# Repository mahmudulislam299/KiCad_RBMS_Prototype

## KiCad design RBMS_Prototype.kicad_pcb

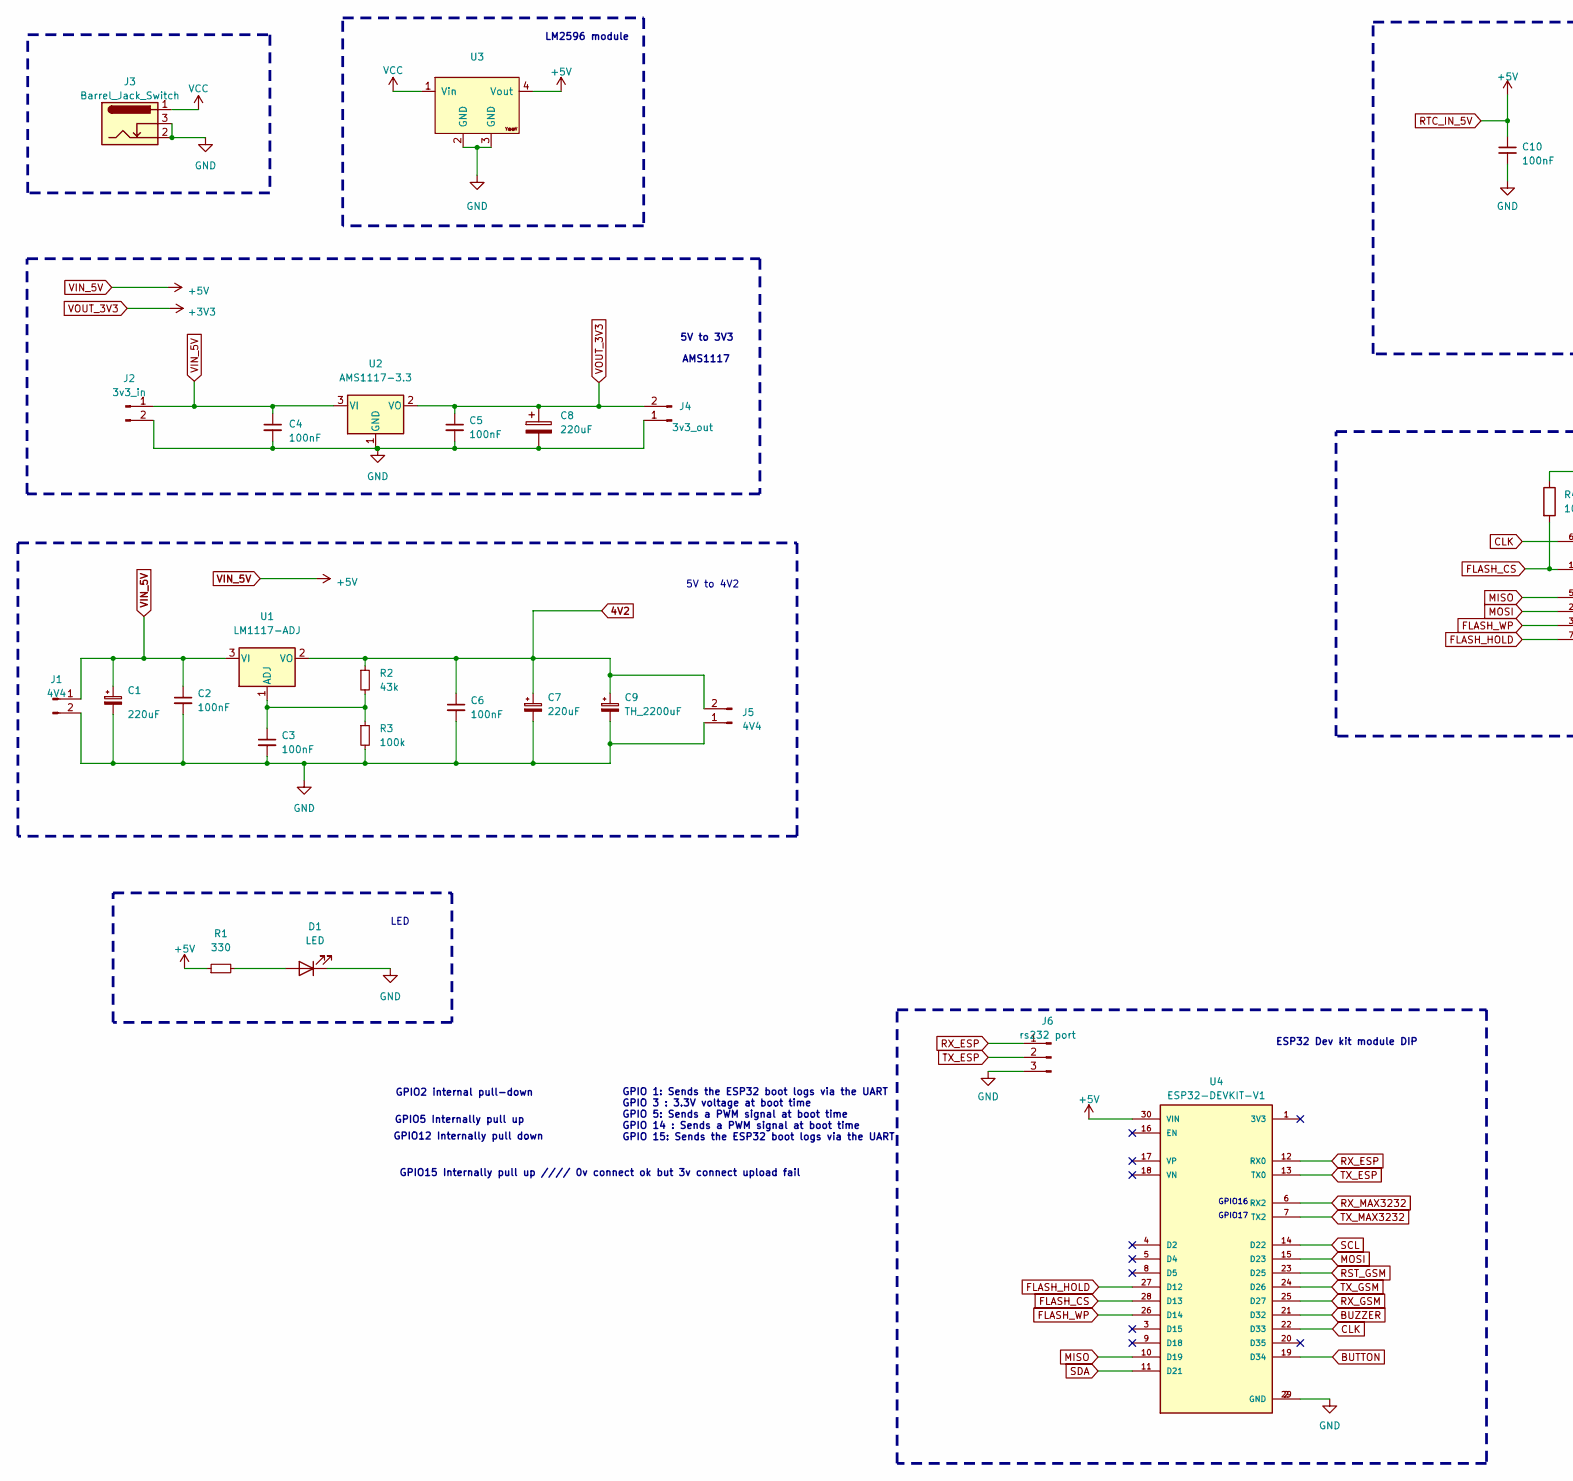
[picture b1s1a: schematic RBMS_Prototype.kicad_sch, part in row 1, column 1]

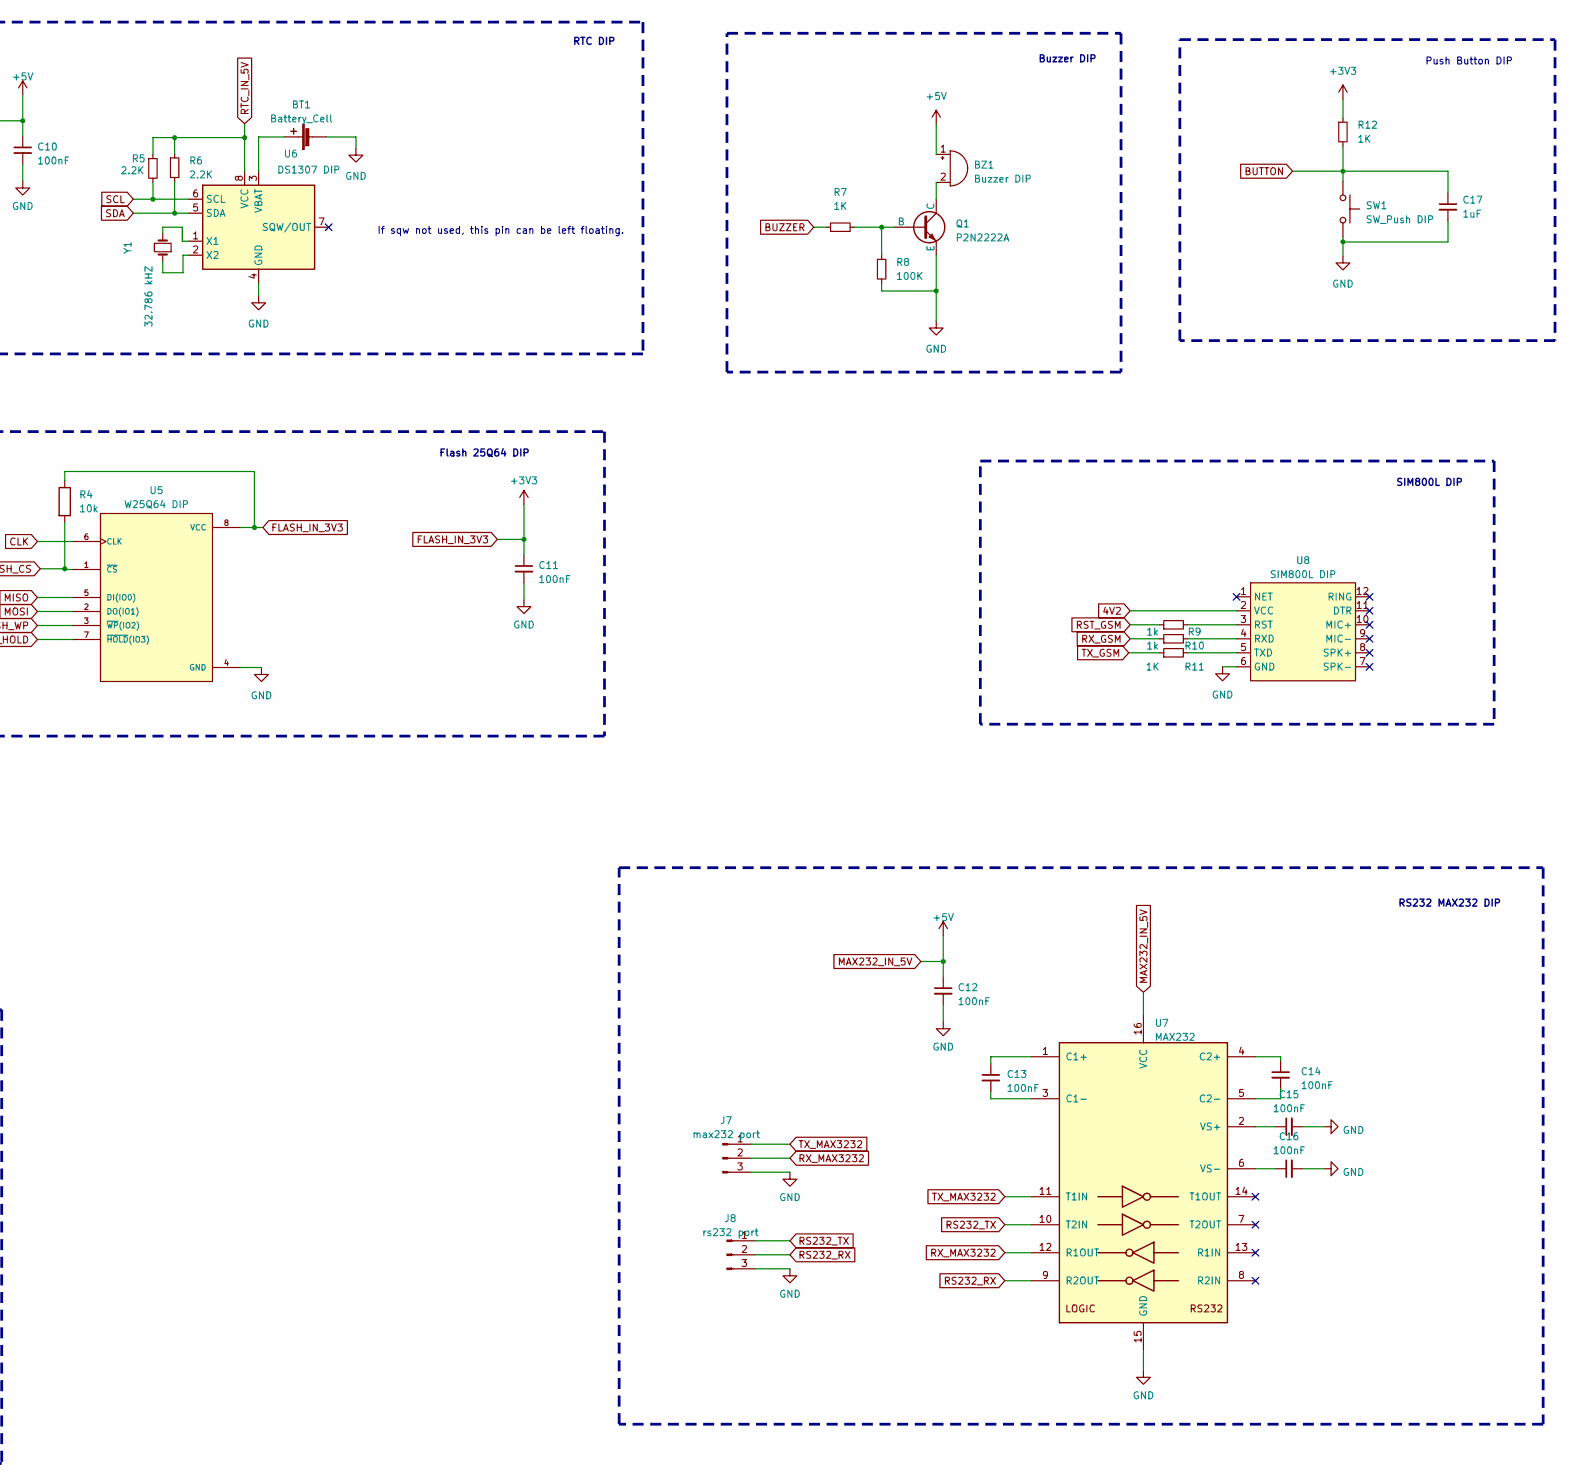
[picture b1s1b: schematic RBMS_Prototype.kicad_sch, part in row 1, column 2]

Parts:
BT1: Battery_Cell; BatteryHolder_Keystone_104_1x23mm
BZ1: Buzzer DIP; Buzzer_12x9.5RM7.6
C1, C7, C8: 220uF; CP_Radial_D8.0mm_P5.00mm
C2, C3, C4, C5, C6, C10, C11, C12, C13, C14, C15, C16: 100nF; C_Disc_D4.7mm_W2.5mm_P5.00mm
C9: TH_2200uF; C_Radial_D12.5mm_H25.0mm_P5.00mm
C17: 1uF; C_Disc_D4.7mm_W2.5mm_P5.00mm
D1: LED; LED_D4.0mm
J1, J5: 4V4; PinHeader_1x02_P2.54mm_Vertical
J2: 3v3_in; PinHeader_1x02_P2.54mm_Vertical
J3: Barrel_Jack_Switch; BarrelJack_Wuerth_6941xx301002
J4: 3v3_out; PinHeader_1x02_P2.54mm_Vertical
J6, J8: rs232 port; PinHeader_1x03_P2.54mm_Vertical
J7: max232 port; PinHeader_1x03_P2.54mm_Vertical
Q1: P2N2222A; TO-92
R1: 330; R_Axial_DIN0207_L6.3mm_D2.5mm_P10.16mm_Horizontal
R2: 43k; R_Axial_DIN0207_L6.3mm_D2.5mm_P10.16mm_Horizontal
R3: 100k; R_Axial_DIN0207_L6.3mm_D2.5mm_P10.16mm_Horizontal
R4: 10k; R_Axial_DIN0207_L6.3mm_D2.5mm_P10.16mm_Horizontal
R5, R6: 2.2K; R_Axial_DIN0207_L6.3mm_D2.5mm_P10.16mm_Horizontal
R7, R11, R12: 1K; R_Axial_DIN0207_L6.3mm_D2.5mm_P10.16mm_Horizontal
R8: 100K; R_Axial_DIN0207_L6.3mm_D2.5mm_P10.16mm_Horizontal
R9, R10: 1k; R_Axial_DIN0207_L6.3mm_D2.5mm_P10.16mm_Horizontal
SW1: SW_Push DIP; SW_Tactile_Straight_KSA0Axx1LFTR
U1: LM1117-ADJ; SOT-223-3_TabPin2
U2: AMS1117-3.3; SOT-223-3_TabPin2
U3: YAAJ_DCDC_StepDown_LM2596
U4: ESP32-DEVKIT-V1; MODULE_ESP32_DEVKIT_V1; PARTREV N/A
U5: W25Q64 DIP; DIP-8_W7.62mm
U6: DS1307 DIP; DIP-8_W7.62mm
U7: MAX232; DIP-16_W7.62mm
U8: SIM800L DIP; SIM800L-CORE
Y1: 32.786 kHZ; Crystal_Round_D1.0mm_Vertical

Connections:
4V2: C6.1, C7.1, C9.1, J5.2, R2.1, U1.2 (VO), U8.2 (VCC)
BUTTON: C17.1, R12.2, SW1.1, U4.19 (D34)
BUZZER: R7.1, U4.21 (D32)
CLK: U4.22 (D33), U5.6 (CLK)
FLASH_CS: R4.2, U4.28 (D13), U5.1 (~CS)
FLASH_HOLD: U4.27 (D12), U5.7 (~HOLD(IO3))
FLASH_IN_3V3: C5.1, C8.1, C11.1, J4.2, R4.1, R12.1, U2.2 (VO), U5.8 (VCC)
FLASH_WP: U4.26 (D14), U5.3 (~WP(IO2))
GND: BT1.2 (-), C1.2, C2.2, C3.2, C4.2, C5.2, C6.2, C7.2, C8.2, C9.2, C10.2, C11.2, C12.2, C15.2, C16.2, C17.2, D1.1 (K), J1.2, J2.2, J3.2, J3.3, J4.1, J5.1, J6.3, J7.3, J8.3, Q1.3 (E), R3.2, R8.2, SW1.2, U2.1 (GND), U3.2 (GND), U3.3 (GND), U4.2 (GND), U4.29 (GND), U5.4 (GND), U6.4 (GND), U7.15 (GND), U8.6 (GND)
MAX232_IN_5V: BZ1.1 (-), C1.1, C2.1, C4.1, C10.1, C12.1, J1.1, J2.1, R1.1, R5.1, R6.1, U1.3 (VI), U2.3 (VI), U3.4 (Vout), U4.30 (VIN), U6.8 (VCC), U7.16 (VCC)
MISO: U4.10 (D19), U5.5 (DI(IO0))
MOSI: U4.15 (D23), U5.2 (DO(IO1))
unnamed: BT1.1 (+), U6.3 (VBAT)
unnamed: BZ1.2 (+), Q1.1 (C)
unnamed: D1.2 (A), R1.2
unnamed: Q1.2 (B), R7.2, R8.1
unnamed: C3.1, R2.2, R3.1, U1.1 (ADJ)
unnamed: U6.1 (X1), Y1.2
unnamed: U6.2 (X2), Y1.1
unnamed: C13.1, U7.1 (C1+)
unnamed: C13.2, U7.3 (C1-)
unnamed: C14.1, U7.4 (C2+)
unnamed: C14.2, U7.5 (C2-)
unnamed: C15.1, U7.2 (VS+)
unnamed: C16.1, U7.6 (VS-)
unnamed: R9.2, U8.3 (RST)
unnamed: R10.2, U8.4 (RXD)
unnamed: R11.2, U8.5 (TXD)
RS232_RX: J8.2, U7.9 (R2OUT)
RS232_TX: J8.1, U7.10 (T2IN)
RST_GSM: R9.1, U4.23 (D25)
RX_ESP: J6.1, U4.12 (RX0)
RX_GSM: R10.1, U4.25 (D27)
RX_MAX3232: J7.2, U4.6 (RX2), U7.12 (R1OUT)
SCL: R5.2, U4.14 (D22), U6.6 (SCL)
SDA: R6.2, U4.11 (D21), U6.5 (SDA)
TX_ESP: J6.2, U4.13 (TX0)
TX_GSM: R11.1, U4.24 (D26)
TX_MAX3232: J7.1, U4.7 (TX2), U7.11 (T1IN)
VCC: J3.1, U3.1 (Vin)

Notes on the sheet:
Flash 25Q64 DIP
LM2596 module
RTC DIP
LED
GPIO 1: Sends the ESP32 boot logs via the UART GPIO 3 : 3.3V voltage at boot time GPIO 5: Sends a PWM signal at boot time GPIO 14 : Sends a PWM signal at boot time GPIO 15: Sends the ESP32 boot logs via the UART
SIM800L DIP
GPIO15 Internally pull up //// 0v connect ok but 3v connect upload fail
GPIO16
5V to 3V3
Buzzer DIP
ESP32 Dev kit module DIP
Push Button DIP
RS232 MAX232 DIP
If sqw not used, this pin can be left floating.
GPIO5 Internally pull up
GPIO17
GPIO12 Internally pull down
5V to 4V2
AMS1117
GPIO2 internal pull-down

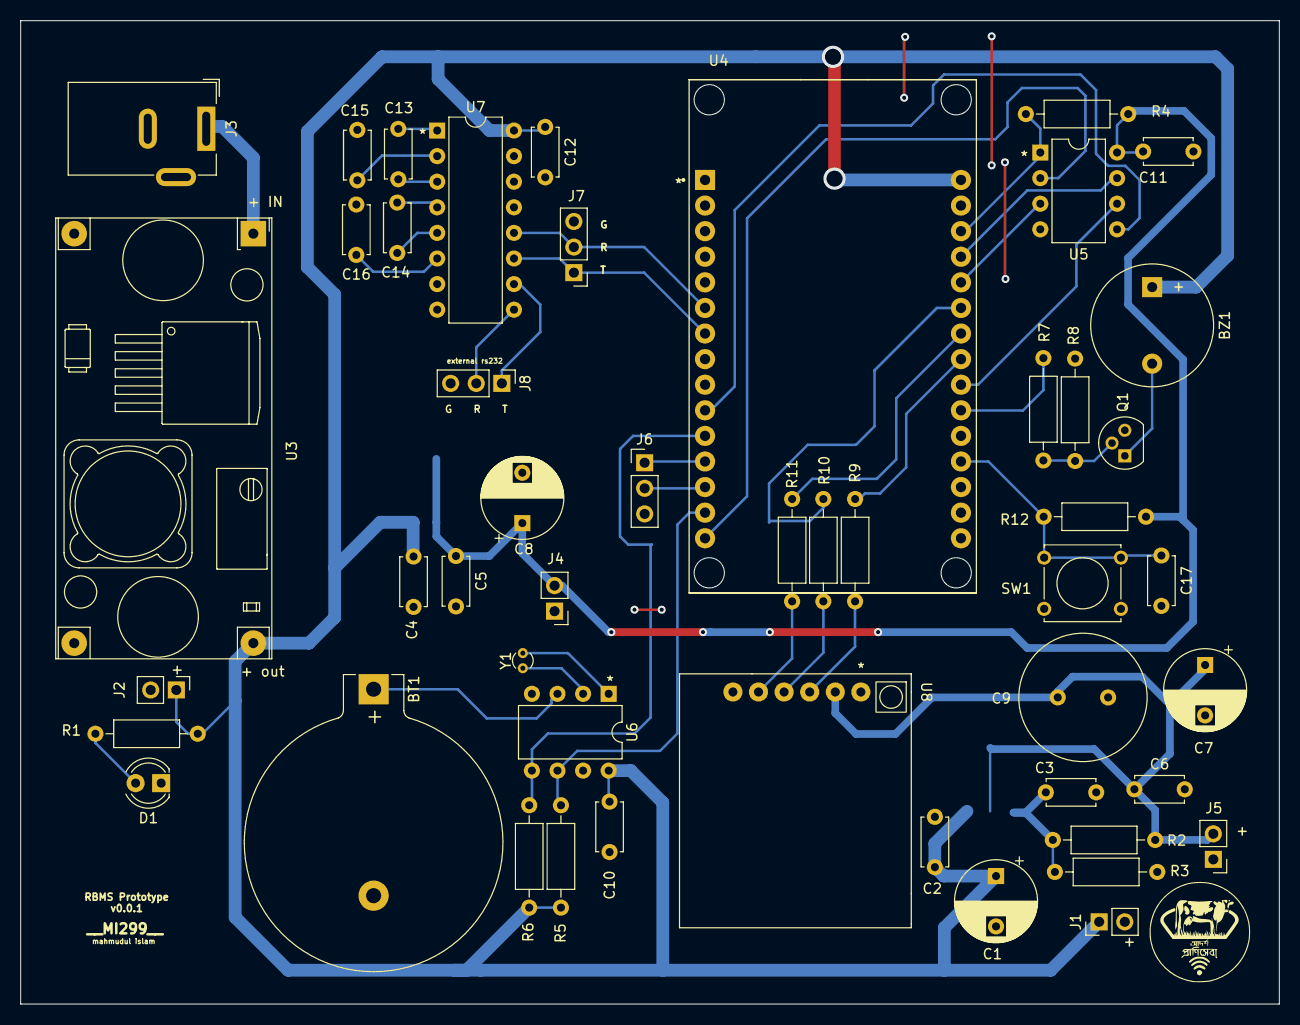
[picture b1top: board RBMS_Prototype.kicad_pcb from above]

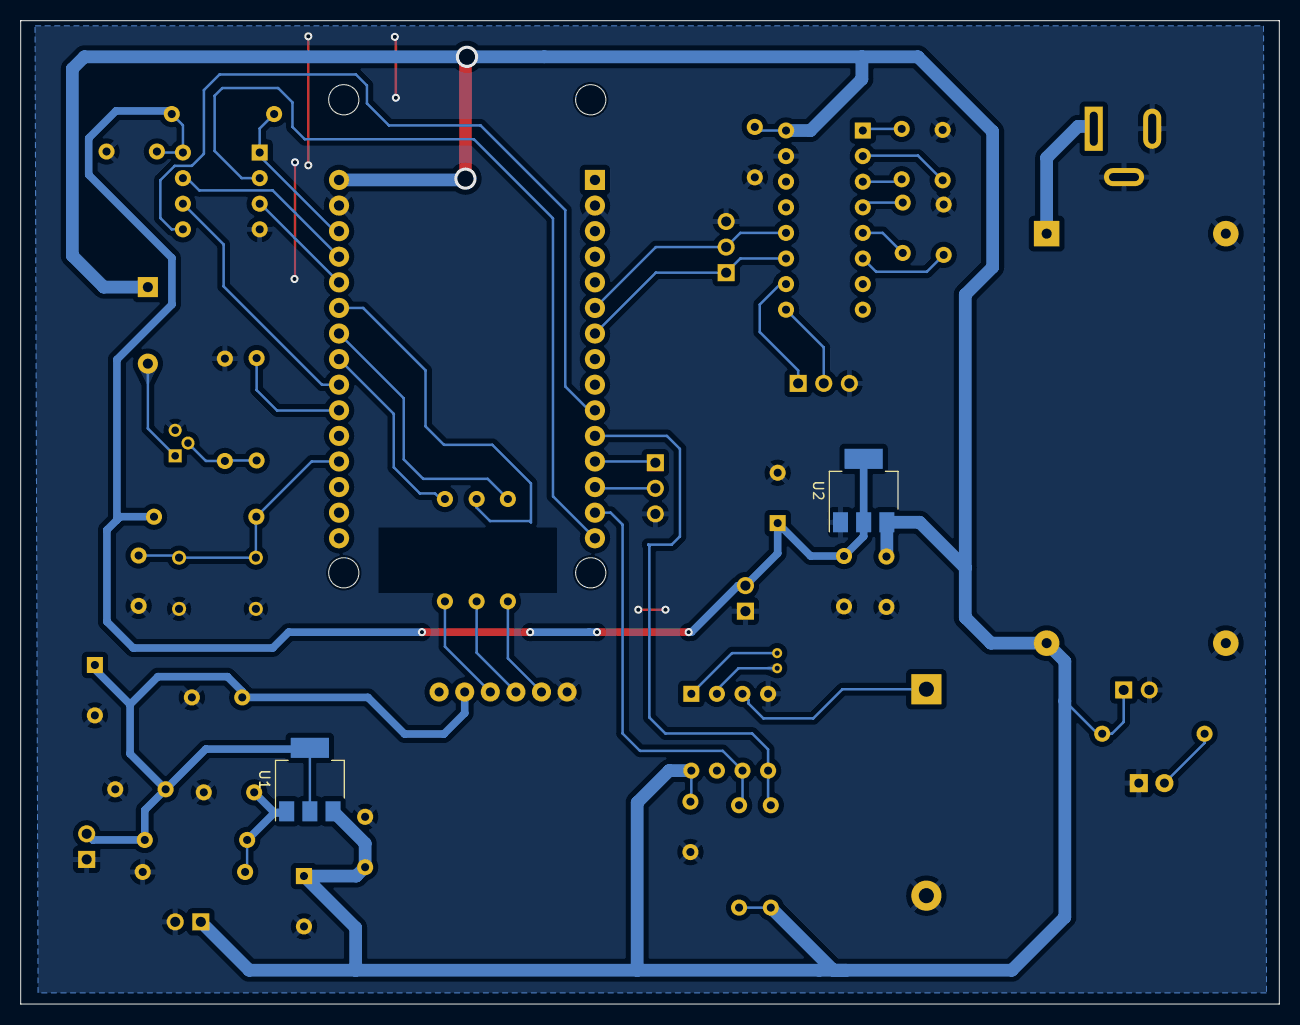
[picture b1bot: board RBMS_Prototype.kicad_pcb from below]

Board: 2 copper layers, 124.9 x 97.6 mm, 51 parts (2 on the bottom side), 40 nets.

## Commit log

2023-05-09 test note added
